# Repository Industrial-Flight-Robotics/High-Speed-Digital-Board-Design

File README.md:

# High Speed Digital Design 
High Speed Digital Board Design using KiCad and the Python SignalIntegrity Library

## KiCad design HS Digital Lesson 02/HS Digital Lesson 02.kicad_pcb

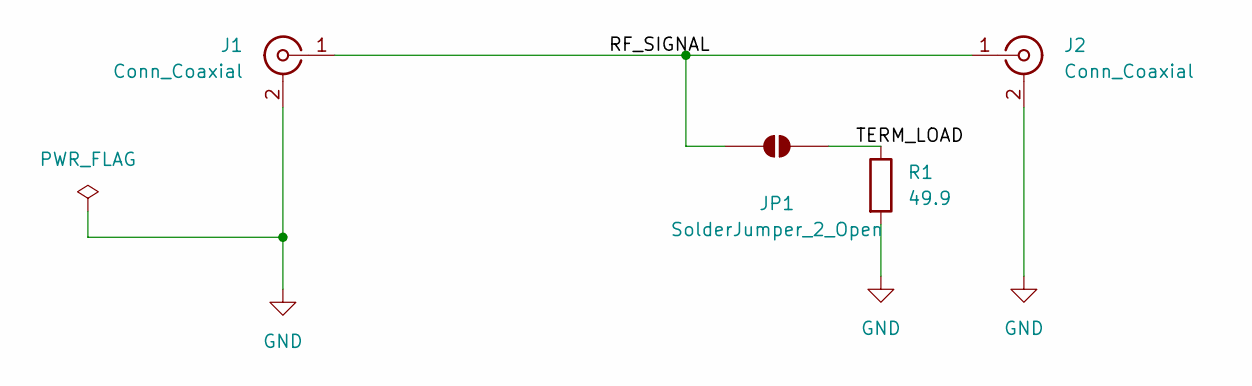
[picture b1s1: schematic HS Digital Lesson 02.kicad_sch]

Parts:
J1, J2: Conn_Coaxial; SMA_Amphenol_132289_EdgeMount
JP1: SolderJumper_2_Open; SolderJumper-2_P1.3mm_Open_Pad1.0x1.5mm
R1: 49.9; R_0805_2012Metric

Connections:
/RF_SIGNAL: J1.1 (In), J2.1 (In), JP1.1 (A)
/TERM_LOAD: JP1.2 (B), R1.1
GND: J1.2 (Ext), J2.2 (Ext), R1.2

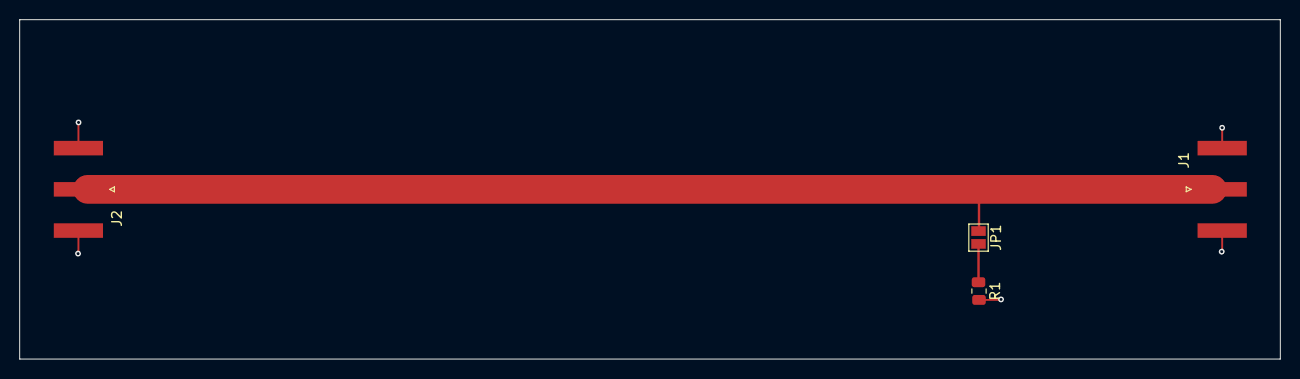
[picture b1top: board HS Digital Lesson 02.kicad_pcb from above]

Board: 4 copper layers, 130.0 x 35.0 mm, 4 parts (0 on the bottom side), 3 nets.
